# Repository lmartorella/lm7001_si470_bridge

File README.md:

# LM7001 FM tuner board upgrade to Si470x 

## Why

I needed a simple replacement for a vintage Pioneer Hi-fi radio tuner that tends to mute quite often. As most Pioneer units of 90's era, his MCU is the core part of the whole system (it receives the IR commands, it displays messages and implements the wake-up timers).

Luckily, the malfunctioning tuner board is based on the LM7001, a direct digital PLL synthesizer with simple serial interface. The PLL works perfectly, so the issue with the jittering sound should be in some other part of the tuner board.

After some hours spent to try to repair the board, I went for the simplest digital upgrade.

## The Silicon Labs module

It is very easy now to found a complete FM tuner with RDS for a couple of dollars from China suppliers. 

The most common core chip is the [Si4702](https://www.silabs.com/audio-and-radio/fm-radios/si4702-03-radio-receivers) from Silicon Labs.

His I2C interface makes it suitable for interfacing to virtually any MCU.

It exposes the mono/stereo state and the tuned flags via I2C: what we need to allow the original Pioneer display to show such information to the user, and to allow auto-scan.

## The Microchip MCU as interface

The computational power to decode the Pioneer MCU commands sent to the LM7001 requires little resources. So I picked up a discontinued but handy 4MHz PIC16F628 from my stock.

> Note: this old PIC supports very little debug facilities. In addition it doesn't support ICSP programming at 3.3V (WTF), so I added a manual jumper to in-circuit program my prototype. Consider any newer non-discontinued 8-bit PIC MCU as an upgrade for your projects. 

In addition to decode the signals to control the LM7001, I wired the MONO signal and sent back the TUNED and STEREO lines as well. In that way all the Pioneer unit functions are fully functionals (all but the AM band).

The 5V TTL lines are converted to 3.3V inputs with resistors, and the two output converted back with a couple of NPNs.

The LM7001 lines are sampled using interrupts (RB0/INT for the chip enable line that triggers the start of transmission, and RB change for the clock line).

_The Pioneer MCU probably implemented the transmission in firmware due to the jittering of the high CLK line._

*IMPORTANT*: The response time from the end of tuning command to when the TUNED signal is drive high in case of valid FM station should be fast enough in order to let the Pioneer MCU to properly scan the frequencies in auto-scan mode.

_In that case, it seems that the unit auto-scans with an interval of ~130ms._

## The final result

The modification here - not looking so professional with all these wires around - is however completely reversible for future reworks.

The board is manaully wired on a small piece of a prototype board to save bucks (but not to save time).

It is fascinating to note that the whole tuner board now fits in the smaller 2x2mm chip in the purple module! The other bigger SSOP8 chip is the on-board headphone amplifier that I didn't even bother to remove.

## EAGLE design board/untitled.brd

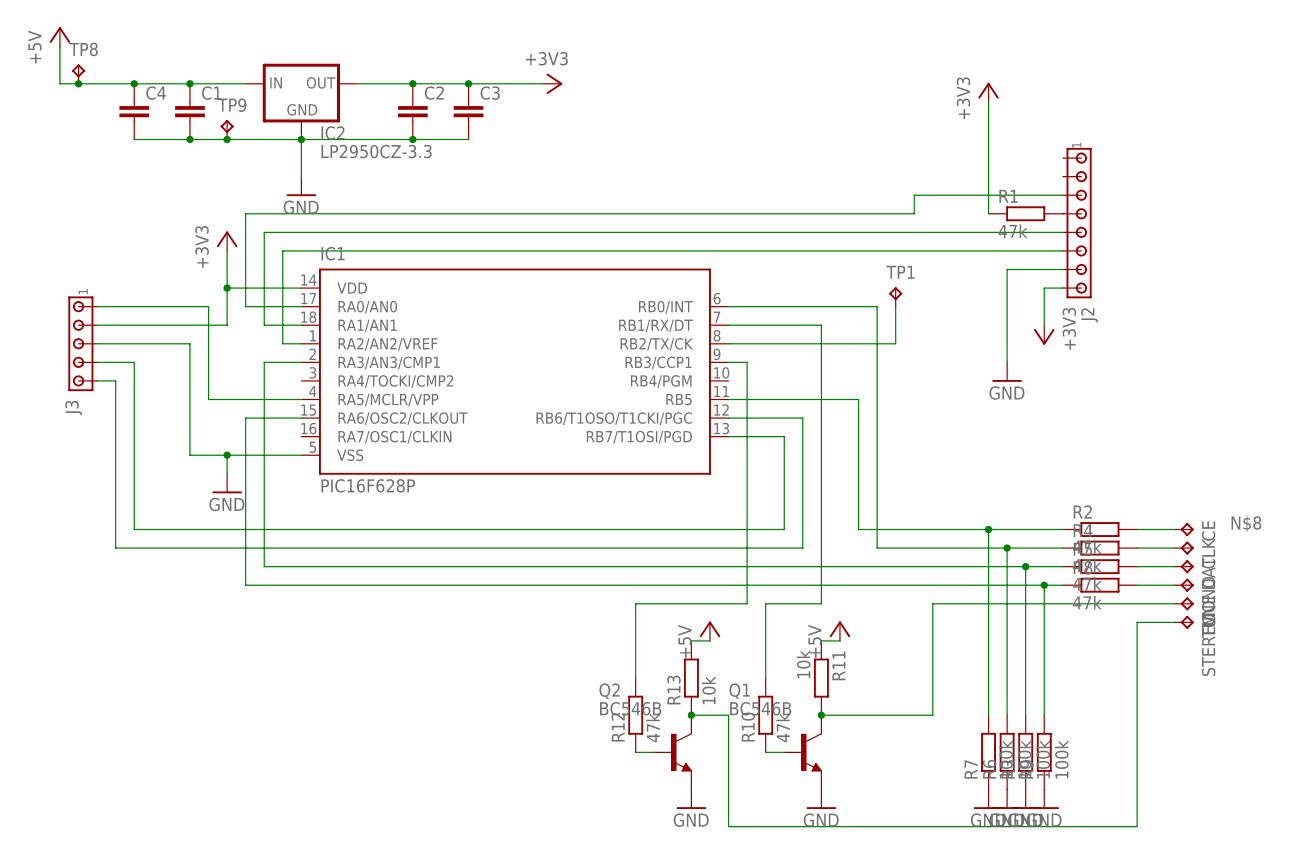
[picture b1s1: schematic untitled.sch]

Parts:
C1, C2, C3, C4: C-EU025-024X044; C025-024X044
CE: TPB1,27; B1,27
CLK: TPB1,27; B1,27
DAT: TPB1,27; B1,27
IC1: PIC16F628P; DIL18
IC2: LP2950CZ-3.3; TO92
J2: MTA08-100; 10X08MTA
J3: MTA05-100; 10X05MTA
MONO: TPB1,27; B1,27
Q1, Q2: BC546B; TO92-EBC
R1, R2, R4, R5, R8, R10, R12: 47k; 0204/7
R3, R6, R7, R9: 100k; 0204/7
R11, R13: 10k; 0204/7
STEREO: TPB1,27; B1,27
TP1, TP8, TP9: TPB1,27; B1,27
TUNE: TPB1,27; B1,27

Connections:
+3V3: C2.1, C3.1, IC1.14 (VDD), IC2.1 (OUT), J2.8, J3.2, R1.1
+5V: C1.1, C4.1, IC2.3 (IN), R11.1, R13.2, TP8.TP
GND: C1.2, C2.2, C3.2, C4.2, IC1.5 (VSS), IC2.2 (GND), J2.7, J3.3, Q1.E, Q2.E, R3.1, R6.1, R7.1, R9.1, TP9.TP
unnamed: IC1.4 (RA5/MCLR/VPP), J3.1
unnamed: IC1.1 (RA2/AN2/VREF), J2.6
unnamed: IC1.18 (RA1/AN1), J2.5
unnamed: IC1.13 (RB7/T1OSI/PGD), J3.4
unnamed: IC1.12 (RB6/T1OSO/T1CKI/PGC), J3.5
unnamed: J2.4, R1.2
unnamed: IC1.17 (RA0/AN0), J2.3
unnamed: CE.TP, R2.2
unnamed: IC1.8 (RB2/TX/CK), TP1.TP
unnamed: CLK.TP, R4.2
unnamed: DAT.TP, R5.2
unnamed: IC1.2 (RA3/AN3/CMP1), R3.2, R5.1
unnamed: IC1.6 (RB0/INT), R4.1, R6.2
unnamed: IC1.11 (RB5), R2.1, R7.2
unnamed: Q1.C, R11.2, TUNE.TP
unnamed: Q1.B, R10.1
unnamed: MONO.TP, R8.2
unnamed: IC1.15 (RA6/OSC2/CLKOUT), R8.1, R9.2
unnamed: Q2.C, R13.1, STEREO.TP
unnamed: IC1.7 (RB1/RX/DT), R10.2
unnamed: Q2.B, R12.1
unnamed: IC1.9 (RB3/CCP1), R12.2

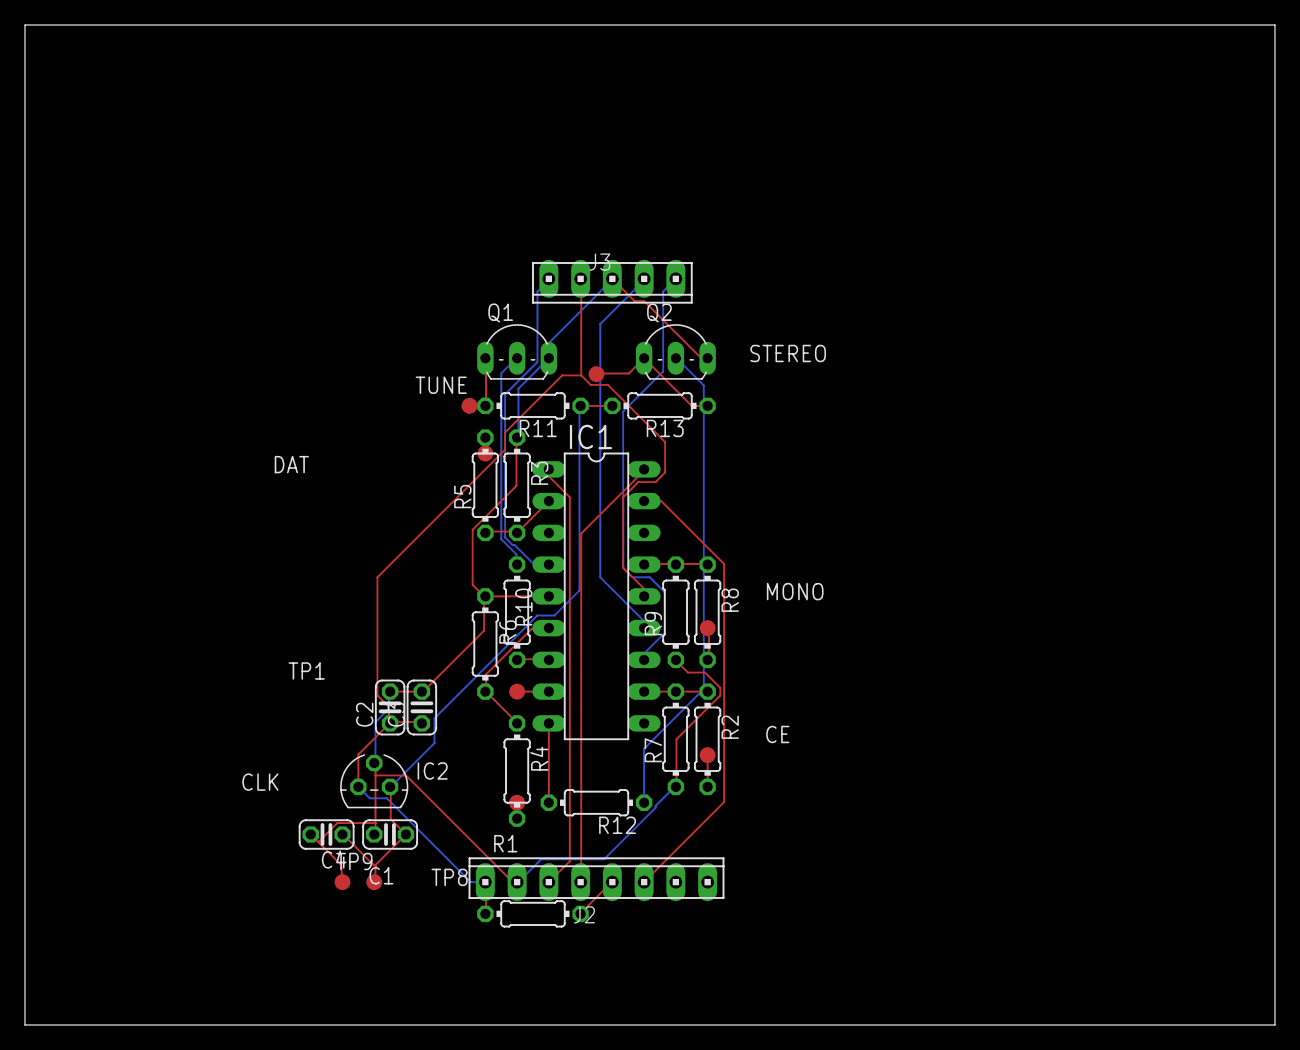
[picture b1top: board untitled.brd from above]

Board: 2 copper layers, 100.0 x 80.0 mm, 32 parts (0 on the bottom side), 25 nets.

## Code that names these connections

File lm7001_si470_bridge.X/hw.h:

// PIC 16F628A
// FOSC 4MHz (internal)
#define _XTAL_FREQ 4000000

// RB1/RB2 (RX/TX) for future expansions and for debug
// RB4/RB6/RB7 for programming interface

#define DEBUG_TX_TRIS TRISBbits.TRISB2
#define DEBUG_TX_PORT PORTBbits.RB2

/**
 * Si4703 interface
 */
// Reset pin
#define SI_RES_TRIS TRISAbits.TRISA0
#define SI_RES_PORT PORTAbits.RA0
// SCK
#define SI_SCK_TRIS TRISAbits.TRISA1
#define SI_SCK_PORT PORTAbits.RA1
// SDA
#define SI_SDA_TRIS TRISAbits.TRISA2
#define SI_SDA_PORT PORTAbits.RA2

/**
 * LM7001 driver interface from Pioneer MCU
 */
// CE on RB5 for interrupt on change
#define MCU_CE_TRIS TRISBbits.TRISB5
#define MCU_CE_PORT PORTBbits.RB5
// Clock on RB0 for interrupt on edge rising
#define MCU_CLK_TRIS TRISBbits.TRISB0
#define MCU_CLK_PORT PORTBbits.RB0

#define MCU_DAT_TRIS TRISAbits.TRISA3
#define MCU_DAT_PORT PORTAbits.RA3

// MONO is active high
#define MCU_MONO_TRIS TRISAbits.TRISA6
#define MCU_MONO_PORT PORTAbits.RA6

// TUNE is active low
#define MCU_TUNE_TRIS TRISBbits.TRISB1
#define MCU_TUNE_PORT PORTBbits.RB1

// STEREO is unknown
#define MCU_STEREO_TRIS TRISBbits.TRISB3
#define MCU_STEREO_PORT PORTBbits.RB3

typedef enum {
    DEBUG_VALID_CODE = 1,
    DEBUG_INVALID_CODE = 2,
    DEBUG_RESET = 3
}
DEBUG_CODES;
void debug(DEBUG_CODES debugCode);

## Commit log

2019-12-01 - Working at protocol bridge, first commit
2019-12-01 - Update during commit
2019-12-05 WIP test in isolation
2019-12-09 - Splitting files to test with Raspberry
2019-12-10 - Bug fixes
2019-12-11 - Fixed i2c
2019-12-11 - Working!
2019-12-11 - Added notes
2020-01-04 Fixed boot timing issues Reenabled WDT
2020-01-04 Fixed AM mute
2020-01-05 - Added docs
